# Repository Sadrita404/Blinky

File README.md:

| Title | Blinky |
| :-- | :---|
|Author |Sadrita Neogi|

## Whta is this ?

It is A 555 LED chaser board — a classic beginner PCB project.

## Why I built this project ?
So this is one of the starter project in the stasis website, so when you went to this guide, I feel like that I want to make something without the SMD components only using the components that can be hand solder , so I went with this project and I learn a lot of things about the KiCad ,etc.

<div align="center">

| PCB and Schematic | |
| :---: | :---: |
|  |  |
|  |  |
|  |  |

<div align="center">
  <h2> Final Look </h2>
  <table border="0" cellpadding="10" cellspacing="0" style="border-collapse: collapse;">
    <tr>
      <!-- FRONT SIDE CARD -->
      <td align="center" valign="top" width="50%" style="background: #ffffff; border: 1px solid #d0d7de; border-radius: 12px; padding: 16px; box-shadow: 0 4px 12px rgba(0,0,0,0.05);">
        
        <div style="margin-top: 12px; font-family: -apple-system, BlinkMacSystemFont, 'Segoe UI', Helvetica, Arial, sans-serif; font-size: 13px; color: #57606a; font-weight: 600; text-transform: uppercase; letter-spacing: 0.5px;">
          ▲ Front Side View
        </div>
      </td>
      <!-- SPACER FOR GITHUB MOBILE DEGRADATION -->
      <td width="2%">&nbsp;</td>
      <!-- BACK SIDE CARD -->
      <td align="center" valign="top" width="50%" style="background: #ffffff; border: 1px solid #d0d7de; border-radius: 12px; padding: 16px; box-shadow: 0 4px 12px rgba(0,0,0,0.05);">
        
        <div style="margin-top: 12px; font-family: -apple-system, BlinkMacSystemFont, 'Segoe UI', Helvetica, Arial, sans-serif; font-size: 13px; color: #57606a; font-weight: 600; text-transform: uppercase; letter-spacing: 0.5px;">
          ▲ Back Side View
        </div>
      </td>
    </tr>
  </table>
</div>
</div>

<div align="center">
  <h2> Bill of Materials </h2>
</div>

| Name | Purpose | Qty | Total (USD) | Link | Distributor |
| :--- | :--- | :---: | :---: | :---: | :--- |
| Blinky Board Kit | Shipped to you - kit project | 1 | $10.00 | - | Hack Club |
| PCB (moq 5) | The Main Board | 5 | $4.00 | [Link](https://jlcpcb.com/) | JLCPCB |
| Shipping PCB	| E- Post (Cheapest) | 	- |	$9.81	| — | 	JLCPCB |
| Total |    |     |   $23.81    |   |    |   |

For this Project I only need the grant of $14 for the PCB and for the other parts it will provided by Hack Club ( Blinky Board Kit) as it is already selected .

**Project Under Hack Club**

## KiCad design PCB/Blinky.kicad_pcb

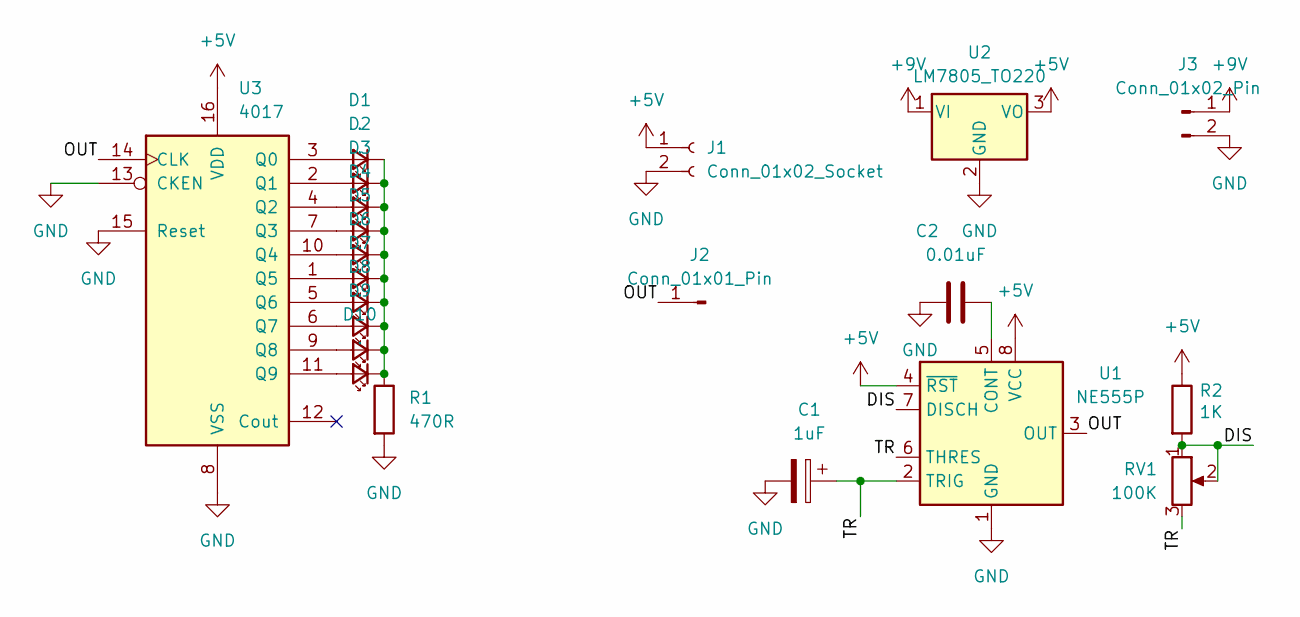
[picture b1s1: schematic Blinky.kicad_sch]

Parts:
C1: 1uF; CP_Radial_D5.0mm_P2.00mm
C2: 0.01uF; C_Disc_D4.3mm_W1.9mm_P5.00mm
D1, D2, D3, D4, D5, D6, D7, D8, D9, D10: .; LED_D5.0mm_FlatTop
J1: Conn_01x02_Socket; PinHeader_1x02_P2.54mm_Vertical
J2: Conn_01x01_Pin; PinHeader_1x01_P2.54mm_Vertical
J3: Conn_01x02_Pin; PinHeader_1x02_P2.54mm_Vertical
R1: 470R; R_Axial_DIN0207_L6.3mm_D2.5mm_P10.16mm_Horizontal
R2: 1K; R_Axial_DIN0207_L6.3mm_D2.5mm_P10.16mm_Horizontal
RV1: 100K; Potentiometer_Bourns_3296W_Vertical
U1: NE555P; DIP-8_W7.62mm
U2: LM7805_TO220; TO-220-3_Vertical
U3: 4017; DIP-16_W7.62mm

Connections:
+5V: J1.1, R2.1, U1.4 (~RST), U1.8 (VCC), U2.3 (VO), U3.16 (VDD)
+9V: J3.1, U2.1 (VI)
/DIS: R2.2, RV1.1, RV1.2, U1.7 (DISCH)
/OUT: J2.1 (Pin_1_1), U1.3 (OUT), U3.14 (CLK)
/TR: C1.1, RV1.3, U1.2 (TRIG), U1.6 (THRES)
GND: C1.2, C2.1, J1.2, J3.2, R1.2, U1.1 (GND), U2.2 (GND), U3.8 (VSS), U3.13 (CKEN), U3.15 (Reset)
unnamed: D1.2 (A), U3.3 (Q0)
unnamed: D1.1 (K), D2.1 (K), D3.1 (K), D4.1 (K), D5.1 (K), D6.1 (K), D7.1 (K), D8.1 (K), D9.1 (K), D10.1 (K), R1.1
unnamed: D2.2 (A), U3.2 (Q1)
unnamed: D3.2 (A), U3.4 (Q2)
unnamed: D4.2 (A), U3.7 (Q3)
unnamed: D5.2 (A), U3.10 (Q4)
unnamed: D6.2 (A), U3.1 (Q5)
unnamed: D7.2 (A), U3.5 (Q6)
unnamed: D8.2 (A), U3.6 (Q7)
unnamed: D9.2 (A), U3.9 (Q8)
unnamed: D10.2 (A), U3.11 (Q9)
unnamed: C2.2, U1.5 (CONT)

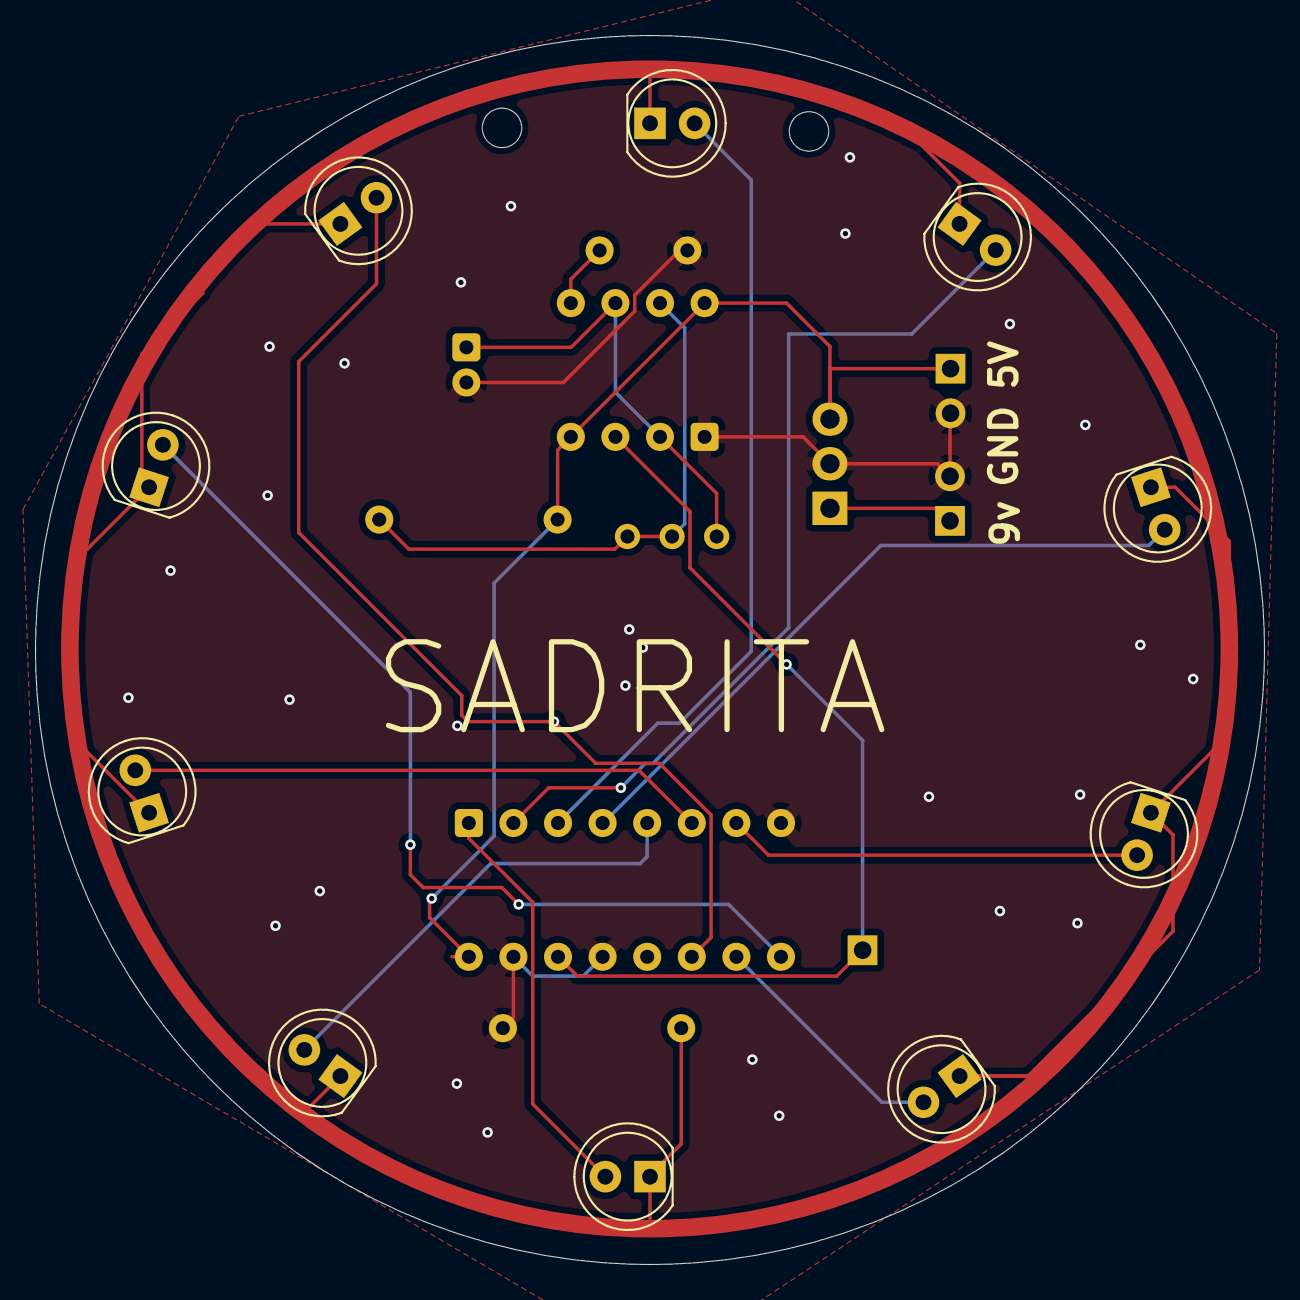
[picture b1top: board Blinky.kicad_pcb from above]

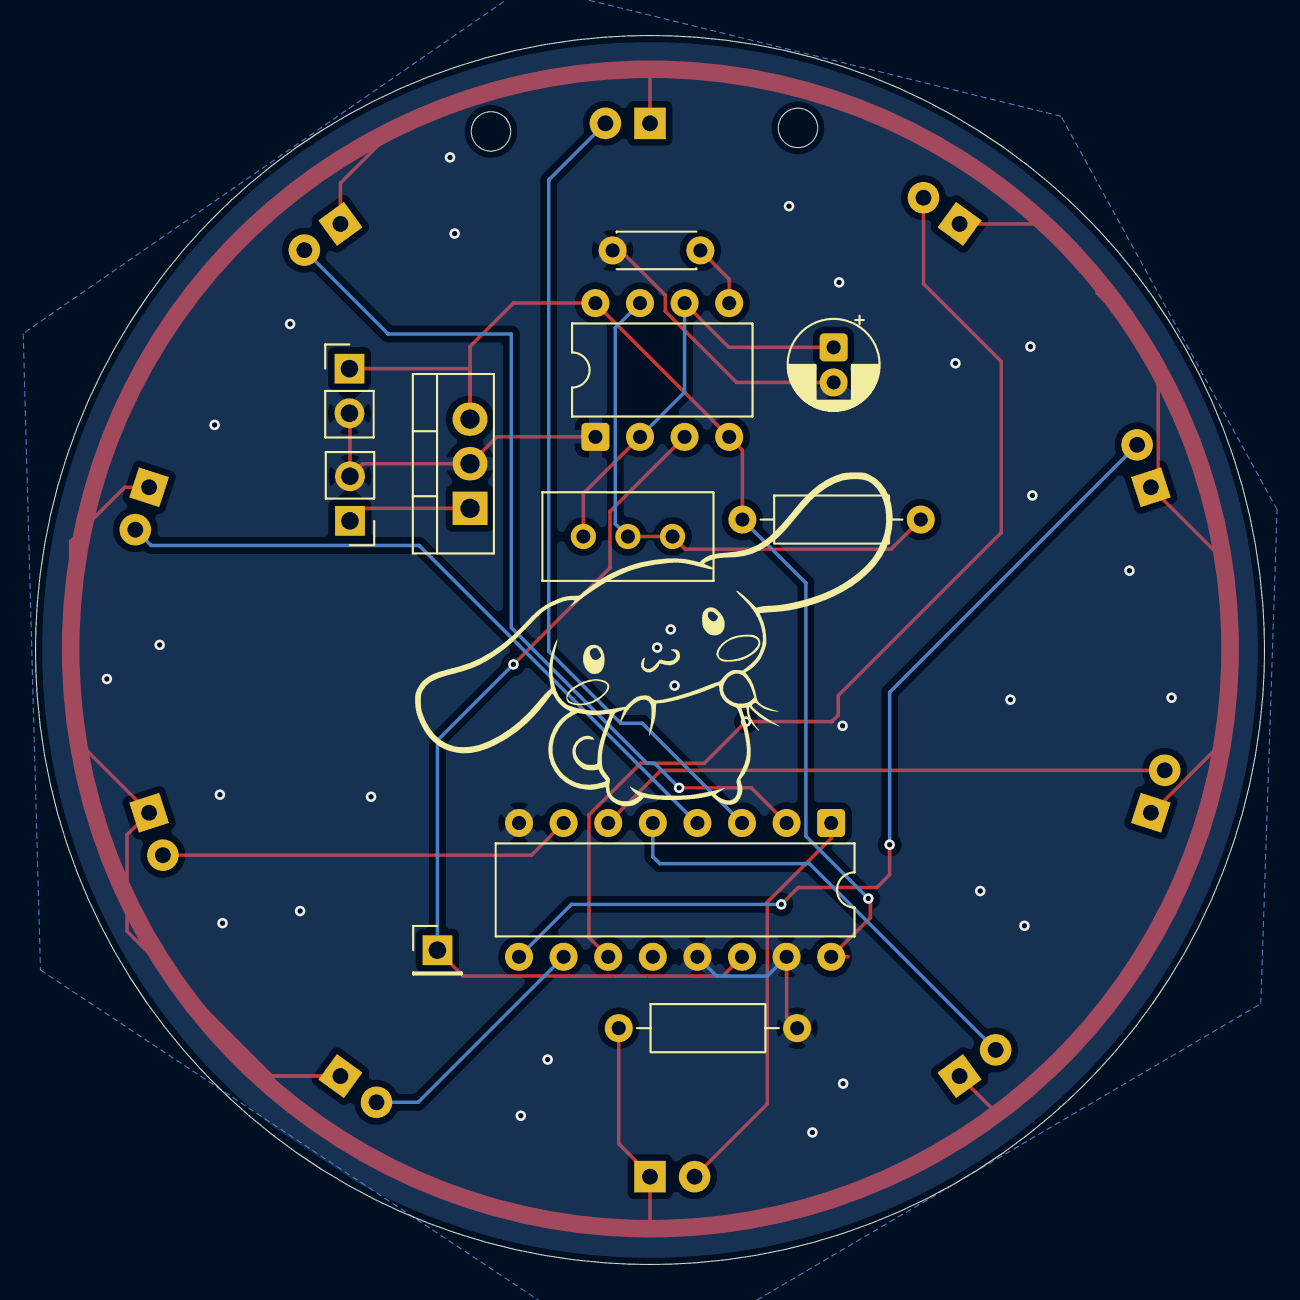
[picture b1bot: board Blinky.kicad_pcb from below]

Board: 2 copper layers, 70.0 x 70.0 mm, 21 parts (11 on the bottom side), 18 nets.
